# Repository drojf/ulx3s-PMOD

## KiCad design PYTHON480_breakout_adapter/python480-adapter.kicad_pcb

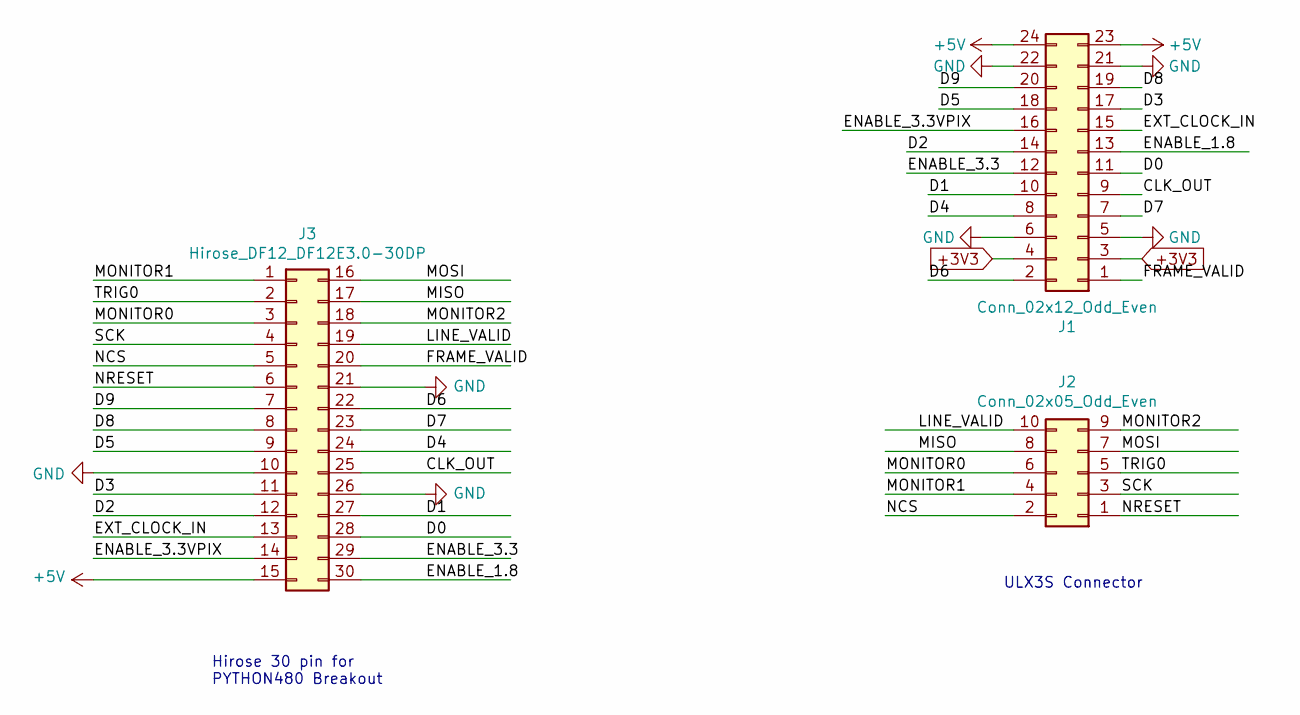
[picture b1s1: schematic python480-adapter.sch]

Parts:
J1: Conn_02x12_Odd_Even; PinHeader_2x12_P2.54mm_Horizontal
J2: Conn_02x05_Odd_Even; PinHeader_2x05_P2.54mm_Horizontal
J3: Hirose_DF12_DF12E3.0-30DP; Hirose_DF12_DF12E3.0-30DP-0.5V_2x15_P0.50mm_Vertical

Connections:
+3V3: J1.3, J1.4
+5V: J1.23, J1.24, J3.15
/CLK_OUT: J1.9, J3.25
/D0: J1.11, J3.28
/D1: J1.10, J3.27
/D2: J1.14, J3.12
/D3: J1.17, J3.11
/D4: J1.8, J3.24
/D5: J1.18, J3.9
/D6: J1.2, J3.22
/D7: J1.7, J3.23
/D8: J1.19, J3.8
/D9: J1.20, J3.7
/ENABLE_1.8: J1.13, J3.30
/ENABLE_3.3: J1.12, J3.29
/ENABLE_3.3VPIX: J1.16, J3.14
/EXT_CLOCK_IN: J1.15, J3.13
/FRAME_VALID: J1.1, J3.20
/LINE_VALID: J2.10, J3.19
/MISO: J2.8, J3.17
/MONITOR0: J2.6, J3.3
/MONITOR1: J2.4, J3.1
/MONITOR2: J2.9, J3.18
/MOSI: J2.7, J3.16
/NCS: J2.2, J3.5
/NRESET: J2.1, J3.6
/SCK: J2.3, J3.4
/TRIG0: J2.5, J3.2
GND: J1.5, J1.6, J1.21, J1.22, J3.10, J3.21, J3.26

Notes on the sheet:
ULX3S Connector
Hirose 30 pin for PYTHON480 Breakout

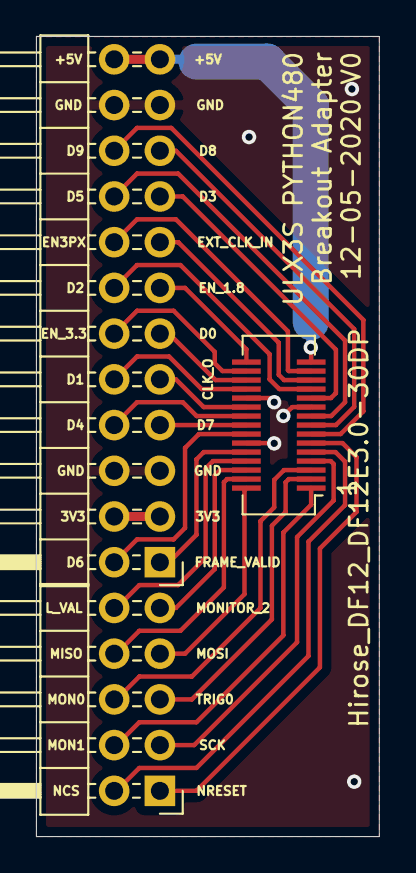
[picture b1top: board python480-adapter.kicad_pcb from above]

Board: 2 copper layers, 19.1 x 44.5 mm, 3 parts (0 on the bottom side), 29 nets.

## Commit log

2020-05-12 Add python480 breakout adapter
2020-05-12 re-label all pins
